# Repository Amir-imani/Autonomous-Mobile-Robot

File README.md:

# Autonomous Mobile Robot

Thesis project: **Design and Construction of a Mobile Robot with Intelligent Path Planning in Dynamic Environments**.

This repository contains the code, electronic design sources, and mechanical models for a differential-drive mobile robot. The software separates time-sensitive low-level control (RP2040), on-board ROS 2 integration (Raspberry Pi 5), and remote vision inference (external compute).

## Start here

- **[Software architecture and complete source guide](docs/SOFTWARE_GUIDE.md)** — subsystem flow, source-file descriptions, dependencies, how to navigate/run the code, and evidence limitations.
- **[Appendix A source index](docs/APPENDIX_CODE_INDEX.md)** — compact software source links for the thesis.
- **[Appendix B electrical design index](docs/APPENDIX_HARDWARE_INDEX.md)** — five circuit schematics, KiCad projects, PCB layouts and available fabrication outputs.
- **[Appendix C mechanical design index](docs/APPENDIX_MECHANICAL_INDEX.md)** — SolidWorks parts, drawings, manufacture quantities and materials.
- **[Code overview](code/README.md)** — package entry points.
- **[Experimental methodology](code/experiments/README.md)** — reproducible source checks, host emulations and hardware prerequisites.

## Repository layout

```text
code/
  firmware/pico/       RP2040 firmware, drivers, Neuro-PID training
  ros2/                Six ROS 2 packages: bridge, model, camera, GPU inference, messages, testbench
  experiments/         Source checks, host benchmarks, controlled emulation and analysis
hardware/              KiCad schematics, PCBs and manufacturing outputs
mechanical/            CAD and exported mechanical drawings
results/               Thesis results directory
docs/                  Appendix index and architecture guide
```

## Implementation scope and evidence

The repository contains closed-loop wheel-control firmware, sensor interfaces, a Pico ↔ Pi binary bridge, wheel odometry, LiDAR sample aggregation, robot description, compressed-image publication, a GPU-capable inference node, and experiment tooling. It does **not** bundle a complete evaluated Nav2/SLAM deployment, a trained ONNX model, or verified physical GPU performance results. Host emulations and software tests must be reported separately from physical measurements.

## Stable thesis citations

For final thesis citations, prefer a full commit-SHA URL (a fixed snapshot) instead of a moving `main` link. A release tag is optional and should only be cited after it actually exists. The repository is private; reviewers need authorized GitHub access.

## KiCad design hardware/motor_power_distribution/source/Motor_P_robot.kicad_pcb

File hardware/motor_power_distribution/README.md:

# Motor Power Distribution Board

This board distributes fused supply power to the robot's drive system and provides connections for an INA-series measurement module. It is a power-distribution board, not the BTS7960 motor driver or embedded motor-control firmware.

## Design files

- [KiCad schematic](source/Motor_P_robot.kicad_sch)
- [KiCad PCB](source/Motor_P_robot.kicad_pcb)
- [KiCad project](source/Motor_P_robot.kicad_pro)

## Manufacturing

Use the editable project as the source for ERC/DRC, pinout review, fabrication outputs and component verification. Check the current-monitor interface and power connector orientation against the as-built robot.

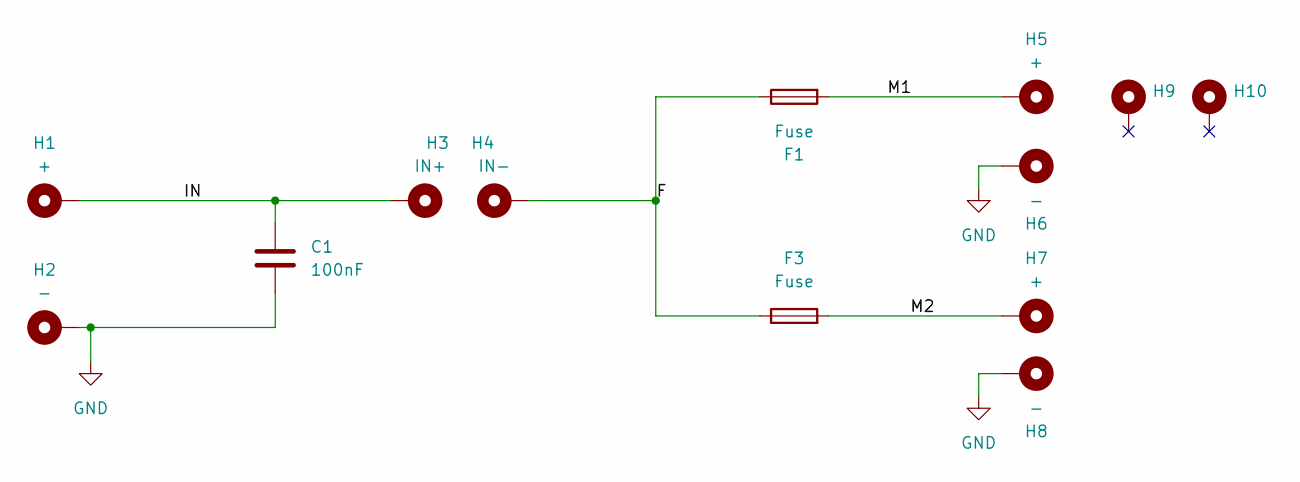
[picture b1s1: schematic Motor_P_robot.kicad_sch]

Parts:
C1: 100nF; C_1206_3216Metric_Pad1.33x1.80mm_HandSolder
F1, F3: Fuse; Fuse_Blade_ATO_directSolder
H1, H5, H7: +; MountingHole_2.2mm_M2_Pad_Via
H2, H6, H8: -; MountingHole_2.2mm_M2_Pad_Via
H3: IN+; MountingHole_2.2mm_M2_Pad_Via
H4: IN-; MountingHole_2.2mm_M2_Pad_Via
H9, H10: MountingHole_3.2mm_M3_Pad_Via

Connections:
/F: F1.1, F3.1, H4.1
/IN: C1.1, H1.1, H3.1
/M1: F1.2, H5.1
/M2: F3.2, H7.1
GND: C1.2, H2.1, H6.1, H8.1

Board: 2 copper layers, 13 parts (0 on the bottom side), 5 nets, no tracks yet.

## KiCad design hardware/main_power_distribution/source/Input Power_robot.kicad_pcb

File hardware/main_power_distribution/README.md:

# Main Power Distribution Board

The main power PCB provides input routing, fuse protection, transient suppression, filtering/bulk capacitors and connection points for an INA-series voltage/current monitoring module. Electrical values and pin assignments are defined in the editable schematic.

## Design files

- [KiCad schematic](source/Input%20Power_robot.kicad_sch)
- [KiCad PCB](source/Input%20Power_robot.kicad_pcb)
- [KiCad project](source/Input%20Power_robot.kicad_pro)

## Manufacturing

The editable KiCad source is the design reference. To manufacture a board, inspect footprints and connector assignments, run ERC/DRC, and generate Gerber/drill outputs from the approved board revision. The mounted INA-series measurement module should be identified from the physical assembly when compiling a final BOM.

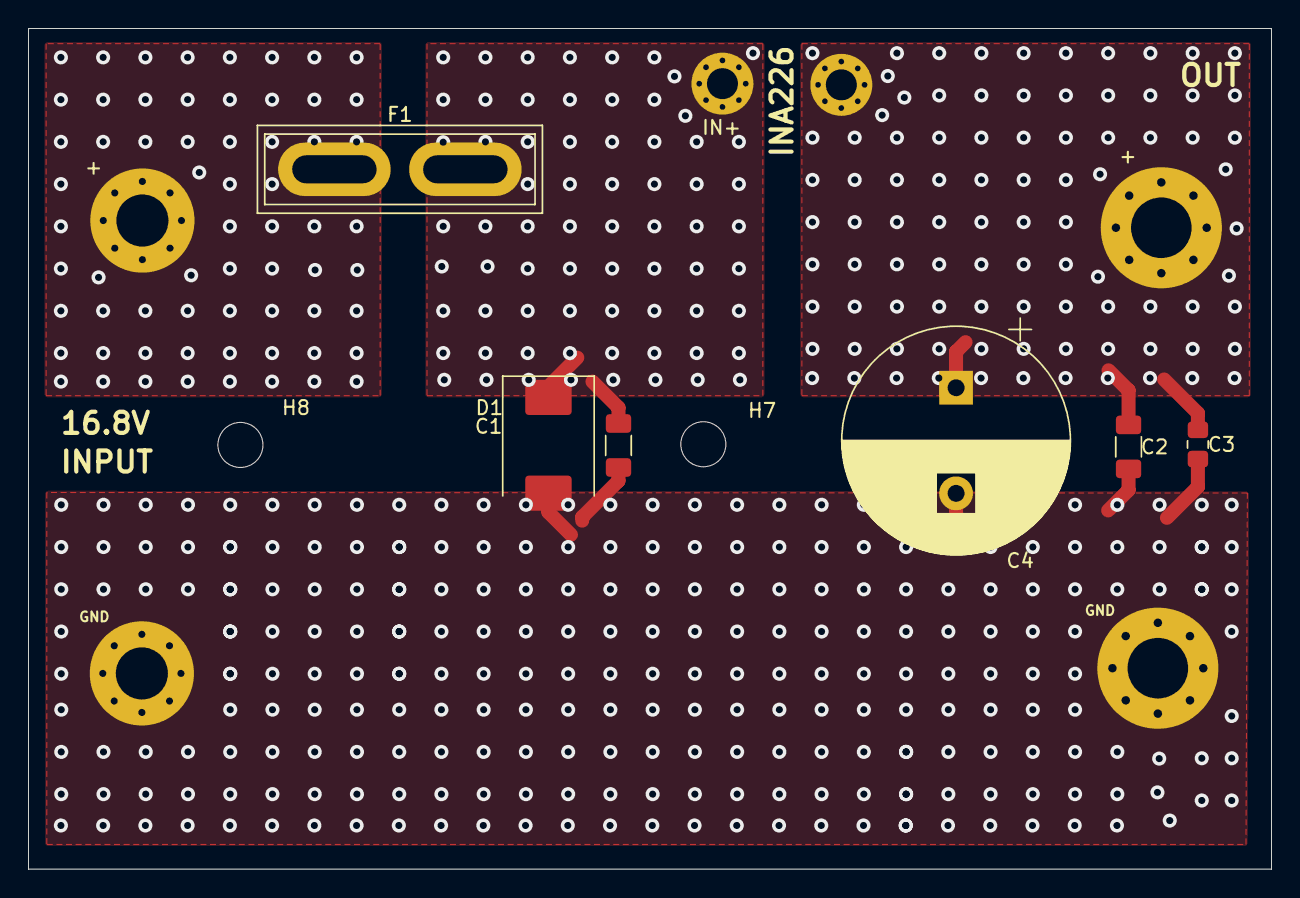
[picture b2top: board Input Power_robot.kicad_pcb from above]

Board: 2 copper layers, 88.3 x 59.7 mm, 14 parts (0 on the bottom side), 4 nets.

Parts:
+: IN; MountingHole_3.7mm_Pad_Via
+#2: OUT; MountingHole_4.3mm_M4_Pad_Via
C1, C2: 100nF; C_1206_3216Metric_Pad1.33x1.80mm_HandSolder
C3: 1uF; C_0805_2012Metric_Pad1.18x1.45mm_HandSolder
C4: 2200uF/35V; CP_Radial_D16.0mm_P7.50mm
D1: SMCJ18CA; D_SMC
F1: Fuse; Fuse_Blade_ATO_directSolder
GND: OUT; MountingHole_4.3mm_M4_Pad_Via
GND#2: IN; MountingHole_3.7mm_Pad_Via
H4: IN-; MountingHole_2.2mm_M2_Pad_Via
H7, H8: P; MountingHole_3.2mm_M3
IN+: IN+; MountingHole_2.2mm_M2_Pad_Via

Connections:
+16.8V: C1.1, D1.1 (A1), F1.2, IN+.1
+16.8V_R: +#2.1, C2.1, C3.1, C4.1, H4.1
+16.8V_U: +.1, F1.1
GND: C1.2, C2.2, C3.2, C4.2, D1.2 (A2), GND.1, GND#2.1

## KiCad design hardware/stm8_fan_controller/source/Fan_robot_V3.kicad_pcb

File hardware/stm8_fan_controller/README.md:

# STM8 Dual-Channel Temperature and Fan Controller

A custom thermal-management PCB for the autonomous mobile robot, based on the STM8S003F3P microcontroller.

## Hardware capabilities
- Two analog NTC thermistor inputs (ADC2 and ADC3).
- Two independently driven PWM fan channels (TIM2_CH1, TIM2_CH2), with TC4428A gate driver and Si9945BDY MOSFET switching stage.
- RGB status indicator driven through transistor stages (TIM1_CH1–CH3), supporting mixed colors.
- UART RX/TX connector for planned communication with the main Raspberry Pi Pico controller.
- SWIM/NRST programming connector.
- 5 V input and AMS1117-3.3 regulator for the logic rail.

## Thesis implementation status

**Hardware designed, fabricated, and mounted on the robot; not used as an active subsystem in the thesis experiments.** The schematics and PCB demonstrate the proposed thermal-management interface, but the board's actual temperature-feedback control, fan PWM response, UART exchange with the Pico, and RGB state logic must **not** be described as experimentally validated. The design repository documents the board at schematic and PCB level; active firmware-level operation is outside the reported experimental evaluation.

## Files

- `source/Fan_robot_V3.kicad_pro`: KiCad project settings.
- `source/Fan_robot_V3.kicad_sch`: Editable schematic.
- `source/Fan_robot_V3.kicad_pcb`: Editable PCB layout.
- `schematic/Fan_robot_V3.pdf`: One-page schematic for independent viewing.
- `images/pcb_3d_top.jpg`: 3D PCB render.

### PCB 3D render

### Schematic

[View schematic PDF](schematic/Fan_robot_V3.pdf)

## Fabrication and verification

Review footprints, connections, and thermal/power ratings using the schematic and PCB, and run ERC/DRC before fabrication. This documentation describes the circuit design and its installed role, not a measured closed-loop thermal-control performance.

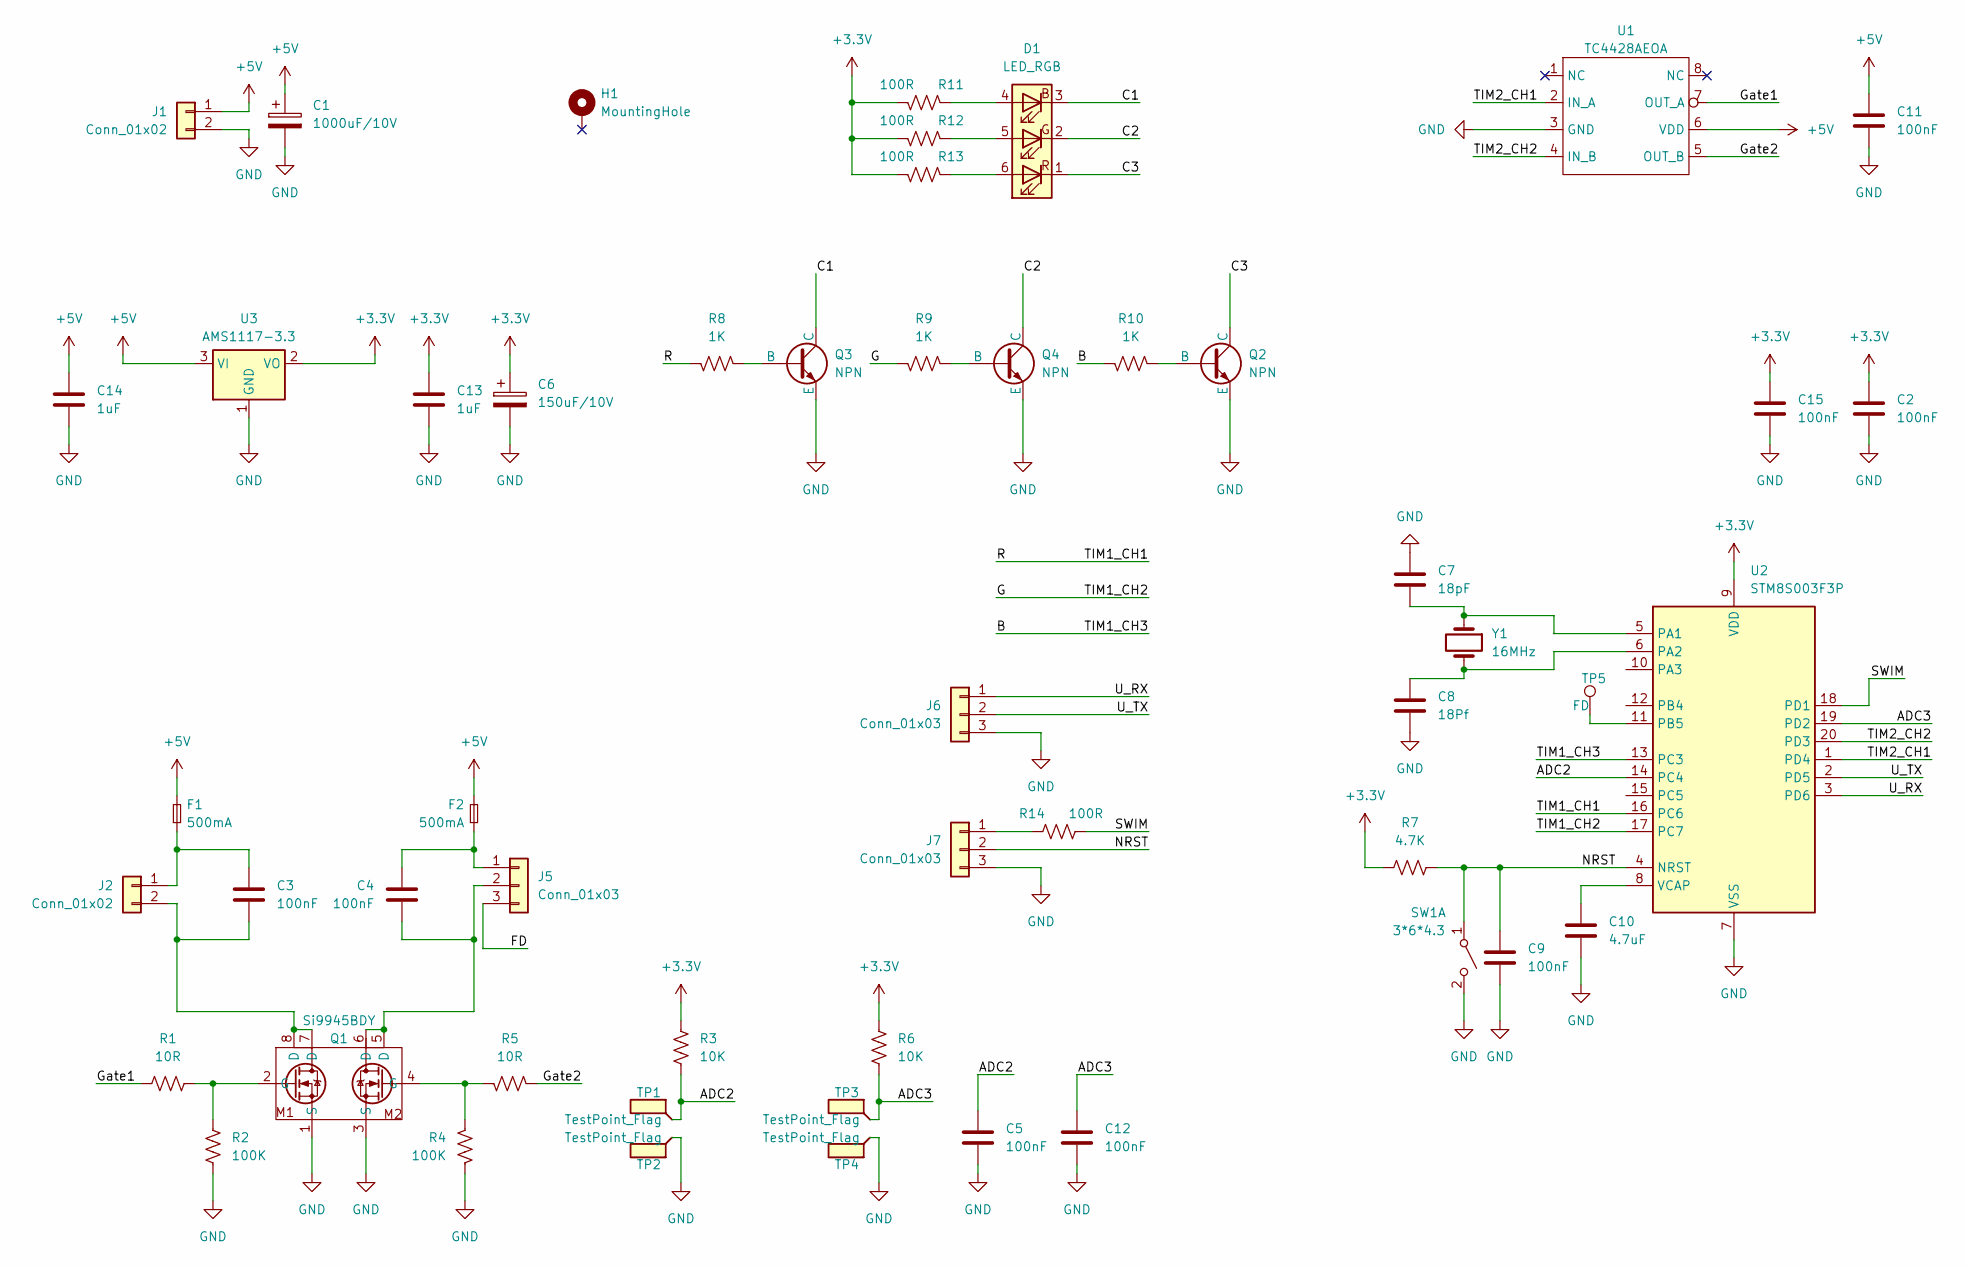
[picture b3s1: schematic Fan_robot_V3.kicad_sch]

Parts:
C1: 1000uF/10V; CP_Radial_D10.0mm_P5.00mm
C2, C3, C4, C5, C9, C11, C12, C15: 100nF; C_0805_2012Metric_Pad1.18x1.45mm_HandSolder
C6: 150uF/10V; CP_Elec_6.3x5.3
C7: 18pF; C_0805_2012Metric_Pad1.18x1.45mm_HandSolder
C8: 18Pf; C_0805_2012Metric_Pad1.18x1.45mm_HandSolder
C10: 4.7uF; C_0805_2012Metric_Pad1.18x1.45mm_HandSolder
C13, C14: 1uF; C_0805_2012Metric_Pad1.18x1.45mm_HandSolder
D1: LED_RGB; LED_RGB_5050-6
F1, F2: 500mA; Fuse_0805_2012Metric_Pad1.15x1.40mm_HandSolder
H1: MountingHole; MountingHole_3.2mm_M3_Pad_Via
J1: Conn_01x02; JST_XH_B2B-XH-A_1x02_P2.50mm_Vertical
J2: Conn_01x02; PinHeader_1x02_P2.54mm_Vertical
J5, J6, J7: Conn_01x03; PinHeader_1x03_P2.54mm_Vertical
Q1: Si9945BDY; PowerIntegrations_SO-8
Q2, Q3, Q4: NPN; SOT-23
R1, R5: 10R; R_0805_2012Metric_Pad1.20x1.40mm_HandSolder
R2, R4: 100K; R_0805_2012Metric_Pad1.20x1.40mm_HandSolder
R3, R6: 10K; R_0805_2012Metric_Pad1.20x1.40mm_HandSolder
R7: 4.7K; R_0805_2012Metric_Pad1.20x1.40mm_HandSolder
R8, R9, R10: 1K; R_0805_2012Metric_Pad1.20x1.40mm_HandSolder
R11, R12, R13, R14: 100R; R_0805_2012Metric_Pad1.20x1.40mm_HandSolder
SW1: 3*6*4.3; SW_Tactile_SPST_NO_Straight_CK_PTS636Sx25SMTRLFS
TP1, TP2, TP3, TP4: TestPoint_Flag; TestPoint_Pad_1.0x1.0mm
TP5: FD; TestPoint_Pad_D1.0mm
U1: TC4428AEOA; PowerIntegrations_SO-8
U2: STM8S003F3P; TSSOP-20_4.4x6.5mm_P0.65mm
U3: AMS1117-3.3; SOT-223-3_TabPin2
Y1: 16MHz; Crystal_SMD_HC49-SD

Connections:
+3.3V: C2.1, C6.1, C13.1, C15.1, R3.2, R6.2, R7.1, R11.2, R12.2, R13.2, U2.9 (VDD), U3.2 (VO)
+5V: C1.1, C11.1, C14.1, F1.2, F2.2, J1.1, U1.6 (VDD), U3.3 (VI)
/ADC2: C5.1, R3.1, TP1.1, U2.14 (PC4)
/ADC3: C12.1, R6.1, TP3.1, U2.19 (PD2)
/B: R10.2, U2.13 (PC3)
/C1: D1.3 (BK), Q3.3 (C)
/C2: D1.2 (GK), Q4.3 (C)
/C3: D1.1 (RK), Q2.3 (C)
/FD: J5.3
/G: R9.2, U2.17 (PC7)
/Gate1: R1.1, U1.7 (OUT_A)
/Gate2: R5.1, U1.5 (OUT_B)
/NRST: C9.1, J7.2, R7.2, SW1.1 (A), U2.4 (NRST)
/R: R8.2, U2.16 (PC6)
/SWIM: R14.2, U2.18 (PD1)
/TIM2_CH1: U1.2 (IN_A), U2.1 (PD4)
/TIM2_CH2: U1.4 (IN_B), U2.20 (PD3)
/U_RX: J6.1, U2.3 (PD6)
/U_TX: J6.2, U2.2 (PD5)
GND: C1.2, C2.2, C5.2, C6.2, C7.1, C8.2, C9.2, C10.2, C11.2, C12.2, C13.2, C14.2, C15.2, J1.2, J6.3, J7.3, Q1.1 (S), Q1.3 (S), Q2.2 (E), Q3.2 (E), Q4.2 (E), R2.1, R4.1, SW1.2 (B), TP2.1, TP4.1, U1.3 (GND), U2.7 (VSS), U3.1 (GND)
unnamed: D1.4 (BA), R11.1
unnamed: D1.5 (GA), R12.1
unnamed: D1.6 (RA), R13.1
unnamed: C3.1, F1.1, J2.1
unnamed: C3.2, J2.2, Q1.7 (D), Q1.8 (D)
unnamed: C4.1, F2.1, J5.1
unnamed: C4.2, J5.2, Q1.5 (D), Q1.6 (D)
unnamed: J7.1, R14.1
unnamed: Q1.2 (G), R1.2, R2.2
unnamed: Q1.4 (G), R4.2, R5.2
unnamed: Q2.1 (B), R10.1
unnamed: Q3.1 (B), R8.1
unnamed: Q4.1 (B), R9.1
unnamed: C7.2, U2.5 (PA1), Y1.1
unnamed: C8.1, U2.6 (PA2), Y1.2
unnamed: TP5.1, U2.11 (PB5)
unnamed: C10.1, U2.8 (VCAP)

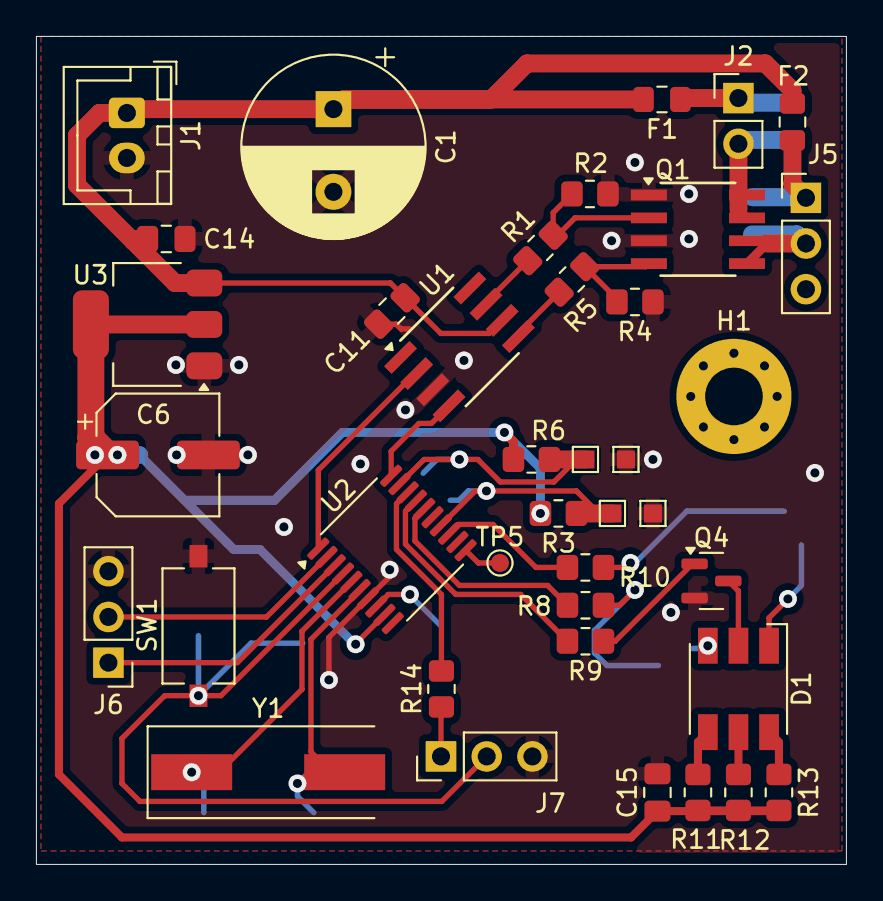
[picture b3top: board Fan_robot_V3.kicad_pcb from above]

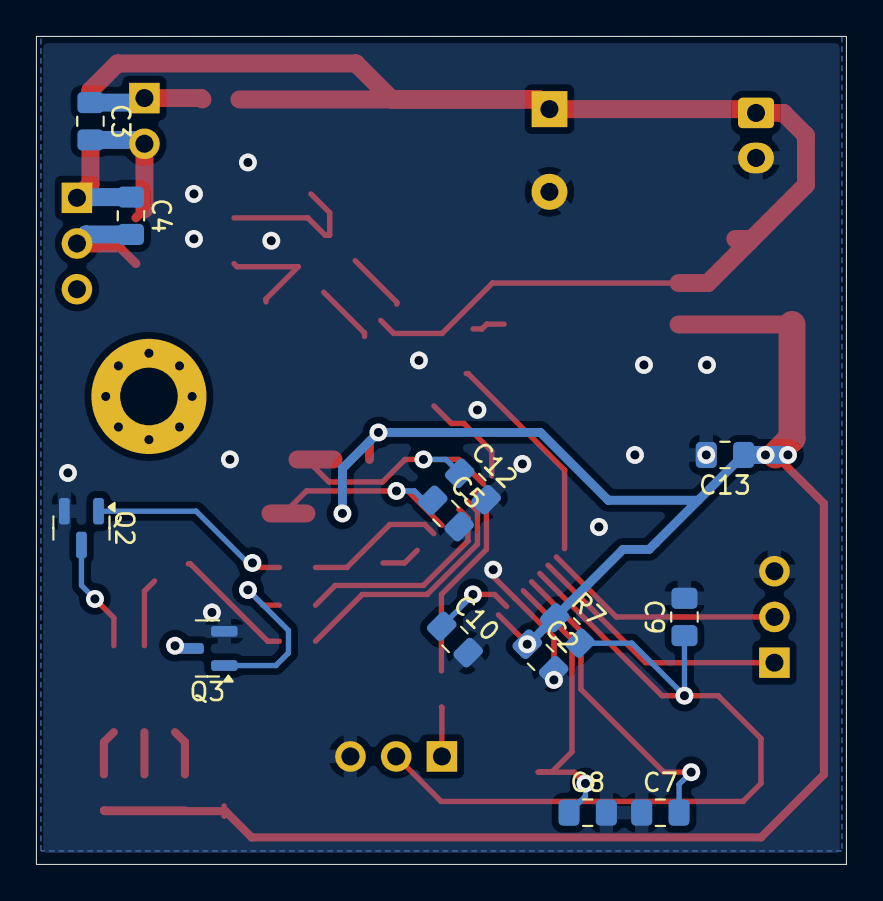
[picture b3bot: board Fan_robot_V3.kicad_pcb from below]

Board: 2 copper layers, 45.0 x 46.0 mm, 52 parts (13 on the bottom side), 36 nets.

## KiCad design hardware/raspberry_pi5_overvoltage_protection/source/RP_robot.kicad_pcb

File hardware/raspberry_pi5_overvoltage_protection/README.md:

# Raspberry Pi 5 Overvoltage Protection Board

This directory contains the KiCad design sources, manufacturing outputs, and design views for the custom Raspberry Pi 5 power-protection board used in the mobile robot.

## Purpose

The board is intended to protect the Raspberry Pi 5 supply rail against an overvoltage event around the 5.1 V threshold. The submitted schematic uses a 5.1 V Zener-triggered crowbar-style protection stage together with a 5 A input fuse and transient suppression.

The editable KiCad source is the authoritative design record. The Gerber and drill files are a fabrication snapshot generated from that design.

## Repository contents

```text
raspberry_pi5_overvoltage_protection/
├── source/
│   ├── RP_robot.kicad_pro
│   ├── RP_robot.kicad_sch
│   └── RP_robot.kicad_pcb
├── fabrication/
│   ├── gerber/
│   │   ├── F_Cu / B_Cu
│   │   ├── F_Mask / B_Mask
│   │   ├── F_Paste / B_Paste
│   │   ├── F_Silkscreen / B_Silkscreen
│   │   ├── Edge_Cuts
│   │   └── Gerber job file
│   └── drill/
│       ├── PTH
│       └── NPTH
└── images/
    ├── pcb_3d_top.png
    └── schematic_view.png
```

## Design views

### 3D PCB render

### Schematic view

## Notes

The schematic snapshot includes the 5.1 V Zener threshold element, a 5 A fuse, an SMBJ5.0A TVS device, and thyristor-based protection devices. Actual trip voltage and fault-clearing behavior depend on component tolerances, fuse characteristics, wiring resistance, and the upstream power source; these should be verified on the physical board before relying on the circuit as the sole protection mechanism.

## Thesis appendix

For the thesis appendix, the schematic view and 3D PCB render are the most useful visual artifacts. The complete KiCad and manufacturing files are preserved here for reproducibility.

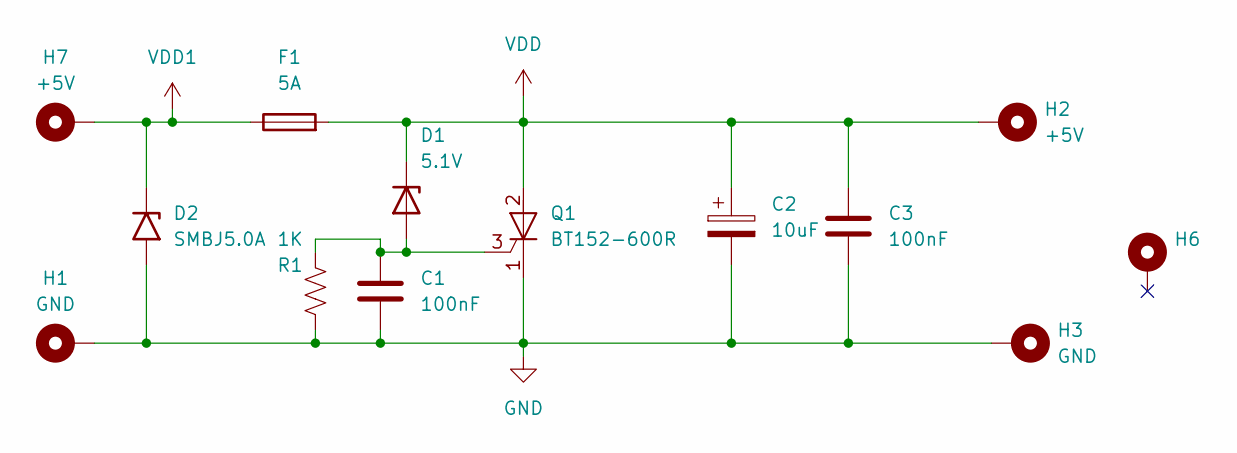
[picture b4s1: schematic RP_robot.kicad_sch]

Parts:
C1, C3: 100nF; C_0805_2012Metric_Pad1.18x1.45mm_HandSolder
C2: 10uF; CP_Elec_6.3x5.3
D1: 5.1V; D_MELF
D2: SMBJ5.0A; D_SMB
F1: 5A; Fuse_1206_3216Metric_Pad1.42x1.75mm_HandSolder
H1, H3: GND; MountingHole_2.2mm_M2_Pad_Via
H2, H7: +5V; MountingHole_2.2mm_M2_Pad_Via
H6: +5V; MountingHole_3.2mm_M3
Q1: BT152-600R; TO-218-3_Horizontal_TabDown
R1: 1K; R_0805_2012Metric_Pad1.20x1.40mm_HandSolder

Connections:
GND: C1.2, C2.2, C3.2, D2.2 (A2), H1.1, H3.1, Q1.1 (K), R1.2
unnamed: C1.1, D1.2 (A), Q1.3 (G), R1.1
VDD: C2.1, C3.1, D1.1 (K), F1.2, H2.1, Q1.2 (A)
VDD1: D2.1 (A1), F1.1, H7.1

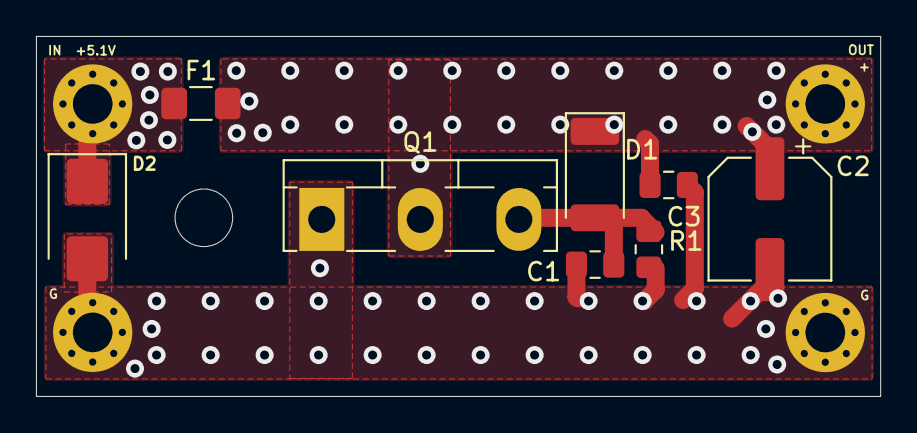
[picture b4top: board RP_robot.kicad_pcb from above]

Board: 2 copper layers, 46.9 x 20.0 mm, 13 parts (0 on the bottom side), 4 nets.

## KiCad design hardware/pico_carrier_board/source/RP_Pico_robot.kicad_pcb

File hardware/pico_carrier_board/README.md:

# Raspberry Pi Pico Carrier / Header Board

This directory contains the hardware design files for the custom Raspberry Pi Pico carrier/header board used in the mobile robot.

## Repository contents

```text
pico_carrier_board/
├── source/
│   ├── RP_Pico_robot.kicad_pro
│   ├── RP_Pico_robot.kicad_sch
│   └── RP_Pico_robot.kicad_pcb
├── fabrication/
│   ├── gerber/
│   │   ├── F_Cu / B_Cu
│   │   ├── F_Mask / B_Mask
│   │   ├── F_Paste / B_Paste
│   │   ├── F_Silkscreen / B_Silkscreen
│   │   ├── Edge_Cuts
│   │   └── Gerber job file
│   └── drill/
│       ├── PTH
│       └── NPTH
└── images/
    ├── pcb_3d_top.jpg
    ├── pcb_3d_bottom.jpg
    └── pcb_layout_editor.jpg
```

## Design role

The board serves as the Raspberry Pi Pico interface/carrier for the robot electronics. It breaks out Pico I/O and power rails through labeled connectors for the robot subsystems and provides the physical integration point between the RP2040 controller and the low-level electronics.

The editable KiCad project under `source/` is the authoritative design source. The Gerber and drill files are manufacturing outputs generated from this design snapshot.

## Design views

### Top-side 3D render

### Bottom-side 3D render

### PCB Editor layout

## Fabrication snapshot

The supplied Gerber and drill outputs were generated by **KiCad/Pcbnew 10.0.3** on **2026-09-11**.

Before ordering a new production batch:

1. Open the editable KiCad project.
2. Run ERC/DRC.
3. Verify footprints and connector orientation against the assembled hardware.
4. Regenerate Gerber and drill files if the source design has changed.

## Thesis appendix

For the thesis appendix, the most useful figures are the PCB Editor layout plus the top and bottom 3D renders. The complete KiCad source and manufacturing outputs remain in the repository so the board can be inspected independently of the thesis document.

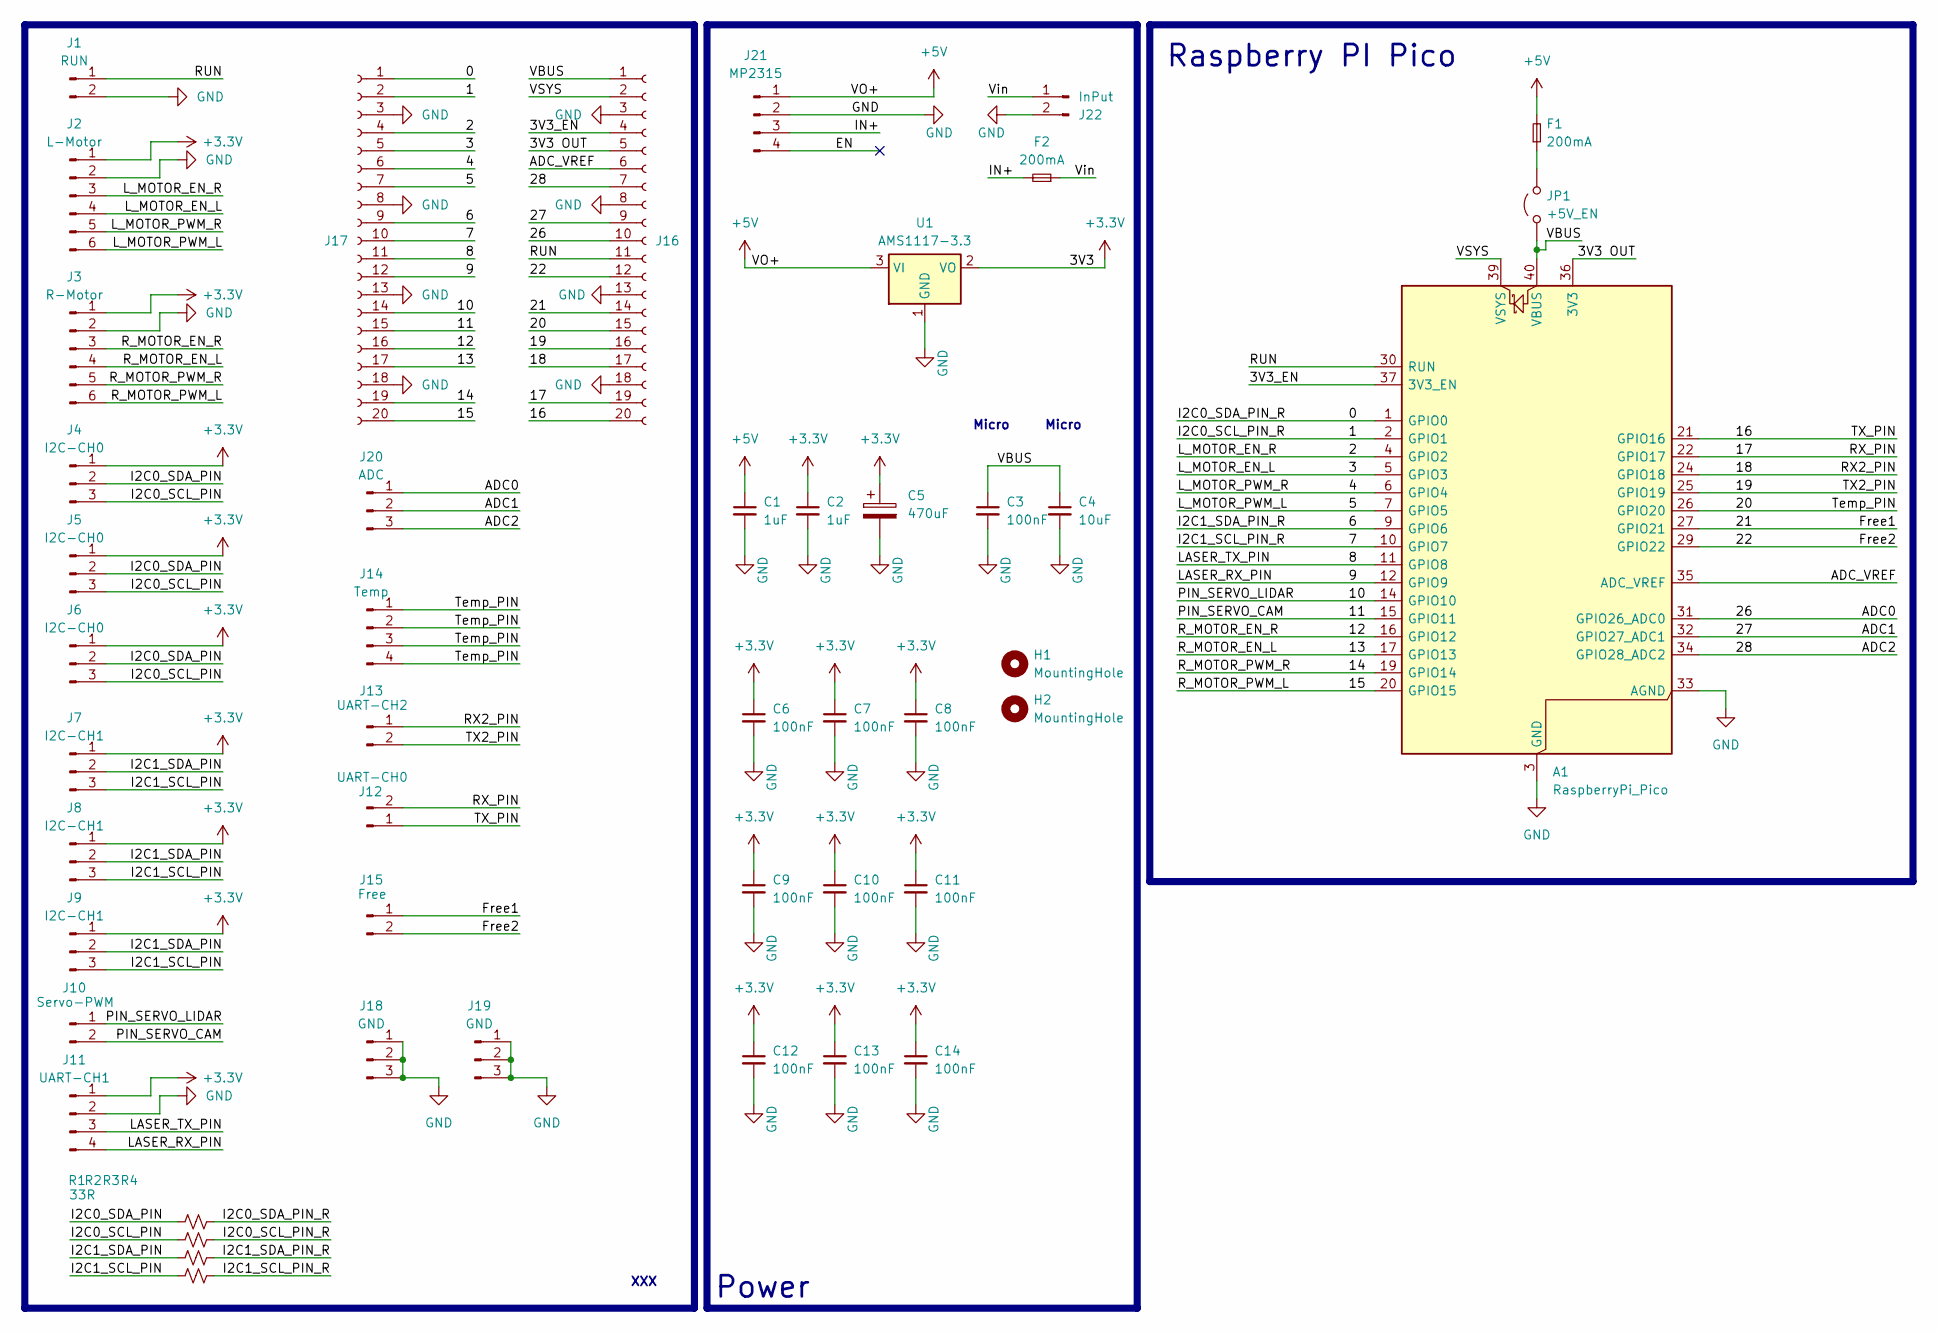
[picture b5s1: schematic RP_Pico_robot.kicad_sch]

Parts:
A1: RaspberryPi_Pico; RaspberryPi_Pico_Common_Unspecified
C1, C2: 1uF; C_0805_2012Metric_Pad1.18x1.45mm_HandSolder
C3, C6, C7, C8, C9, C10, C11, C12, C13, C14: 100nF; C_0805_2012Metric_Pad1.18x1.45mm_HandSolder
C4: 10uF; C_0805_2012Metric_Pad1.18x1.45mm_HandSolder
C5: 470uF; CP_Radial_D8.0mm_P3.80mm
F1, F2: 200mA; Fuse_0805_2012Metric_Pad1.15x1.40mm_HandSolder
H1, H2: MountingHole; MountingHole_3mm_Pad_Via
J1: RUN; JST_XH_B2B-XH-A_1x02_P2.50mm_Vertical
J2: L-Motor; JST_XH_B6B-XH-A_1x06_P2.50mm_Vertical
J3: R-Motor; JST_XH_B6B-XH-A_1x06_P2.50mm_Vertical
J4, J5, J6: I2C-CH0; JST_XH_B3B-XH-A_1x03_P2.50mm_Vertical
J7, J8, J9: I2C-CH1; JST_XH_B3B-XH-A_1x03_P2.50mm_Vertical
J10: Servo-PWM; JST_XH_B2B-XH-A_1x02_P2.50mm_Vertical
J11: UART-CH1; JST_XH_B4B-XH-A_1x04_P2.50mm_Vertical
J12: UART-CH0; JST_XH_B2B-XH-A_1x02_P2.50mm_Vertical
J13: UART-CH2; JST_XH_B2B-XH-A_1x02_P2.50mm_Vertical
J14: Temp; JST_XH_B4B-XH-A_1x04_P2.50mm_Vertical
J15: Free; JST_XH_B2B-XH-A_1x02_P2.50mm_Vertical
J16, J17: Conn_01x20_Socket; PinHeader_1x20_P2.54mm_Vertical
J18, J19: GND; JST_XH_B3B-XH-A_1x03_P2.50mm_Vertical
J20: ADC; JST_XH_B3B-XH-A_1x03_P2.50mm_Vertical
J21: MP2315; PinHeader_1x04_P2.54mm_Vertical
J22: InPut; JST_XH_B2B-XH-A_1x02_P2.50mm_Vertical
JP1: +5V_EN; TestPoint_2Pads_Pitch2.54mm_Drill0.8mm
R1, R2, R3, R4: 33R; R_0805_2012Metric_Pad1.20x1.40mm_HandSolder
U1: AMS1117-3.3; SOT-223-3_TabPin2

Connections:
+3.3V: C2.1, C5.1, C6.1, C7.1, C8.1, C9.1, C10.1, C11.1, C12.1, C13.1, C14.1, J2.1, J3.1, J4.1, J5.1, J6.1, J7.1, J8.1, J9.1, J11.1, U1.2 (VO)
+5V: C1.1, F1.2, J21.1, U1.3 (VI)
/0: A1.1 (GPIO0), J17.1, R1.2
/1: A1.2 (GPIO1), J17.2, R2.2
/2: A1.4 (GPIO2), J2.3, J17.4
/3: A1.5 (GPIO3), J2.4, J17.5
/3V3 OUT: A1.36 (3V3), J16.5
/3V3_EN: A1.37 (3V3_EN), J16.4
/4: A1.6 (GPIO4), J2.5, J17.6
/5: A1.7 (GPIO5), J2.6, J17.7
/6: A1.9 (GPIO6), J17.9, R3.2
/7: A1.10 (GPIO7), J17.10, R4.2
/8: A1.11 (GPIO8), J11.3, J17.11
/9: A1.12 (GPIO9), J11.4, J17.12
/10: A1.14 (GPIO10), J10.1, J17.14
/11: A1.15 (GPIO11), J10.2, J17.15
/12: A1.16 (GPIO12), J3.3, J17.16
/13: A1.17 (GPIO13), J3.4, J17.17
/14: A1.19 (GPIO14), J3.5, J17.19
/15: A1.20 (GPIO15), J3.6, J17.20
/16: A1.21 (GPIO16), J12.1, J16.20
/17: A1.22 (GPIO17), J12.2, J16.19
/18: A1.24 (GPIO18), J13.1, J16.17
/19: A1.25 (GPIO19), J13.2, J16.16
/20: A1.26 (GPIO20), J14.1, J14.2, J14.3, J14.4, J16.15
/21: A1.27 (GPIO21), J15.1, J16.14
/22: A1.29 (GPIO22), J15.2, J16.12
/26: A1.31 (GPIO26_ADC0), J16.10, J20.1
/27: A1.32 (GPIO27_ADC1), J16.9, J20.2
/28: A1.34 (GPIO28_ADC2), J16.7, J20.3
/ADC_VREF: A1.35 (ADC_VREF), J16.6
/EN: J21.4
/I2C0_SCL_PIN: J4.3, J5.3, J6.3, R2.1
/I2C0_SDA_PIN: J4.2, J5.2, J6.2, R1.1
/I2C1_SCL_PIN: J7.3, J8.3, J9.3, R4.1
/I2C1_SDA_PIN: J7.2, J8.2, J9.2, R3.1
/IN+: F2.2, J21.3
/RUN: A1.30 (RUN), J1.1, J16.11
/VBUS: A1.40 (VBUS), C3.1, C4.1, J16.1, JP1.1 (A)
/VSYS: A1.39 (VSYS), J16.2
/Vin: F2.1, J22.1
GND: A1.3 (GND), A1.8 (GND), A1.13 (GND), A1.18 (GND), A1.23 (GND), A1.28 (GND), A1.33 (AGND), A1.38 (GND), C1.2, C2.2, C3.2, C4.2, C5.2, C6.2, C7.2, C8.2, C9.2, C10.2, C11.2, C12.2, C13.2, C14.2, J1.2, J2.2, J3.2, J11.2, J16.3, J16.8, J16.13, J16.18, J17.3, J17.8, J17.13, J17.18, J18.1, J18.2, J18.3, J19.1, J19.2, J19.3, J21.2, J22.2, U1.1 (GND)
unnamed: F1.1, JP1.2 (B)

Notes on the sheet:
XXX
Raspberry PI Pico
Micro
Power

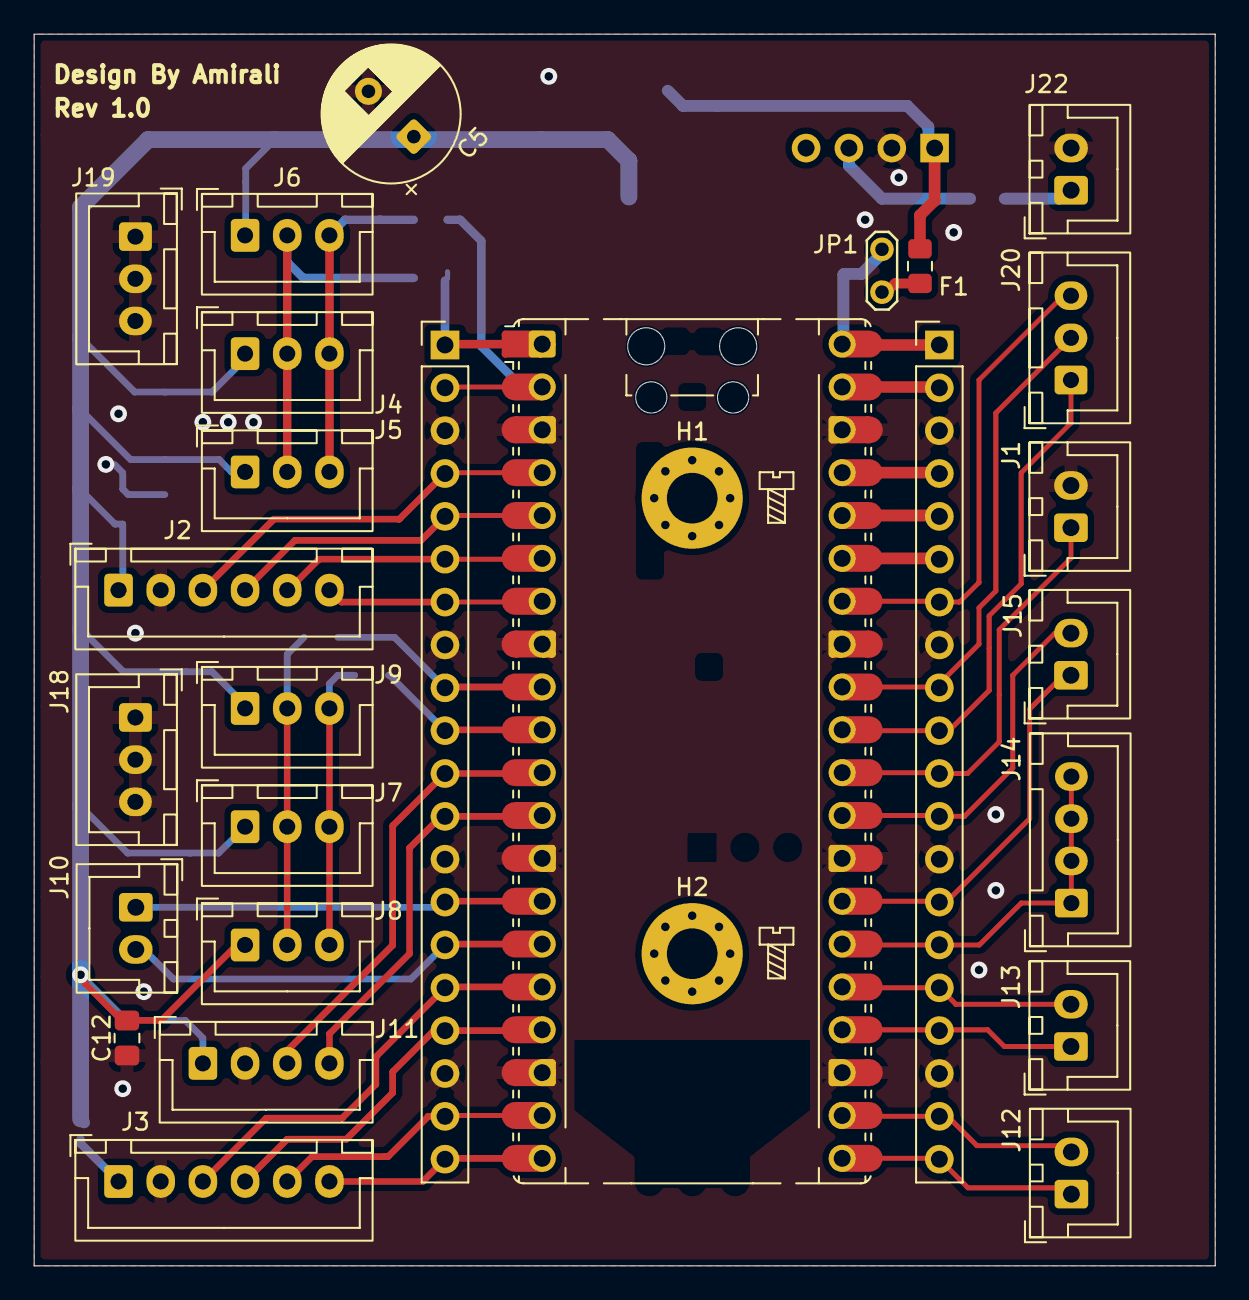
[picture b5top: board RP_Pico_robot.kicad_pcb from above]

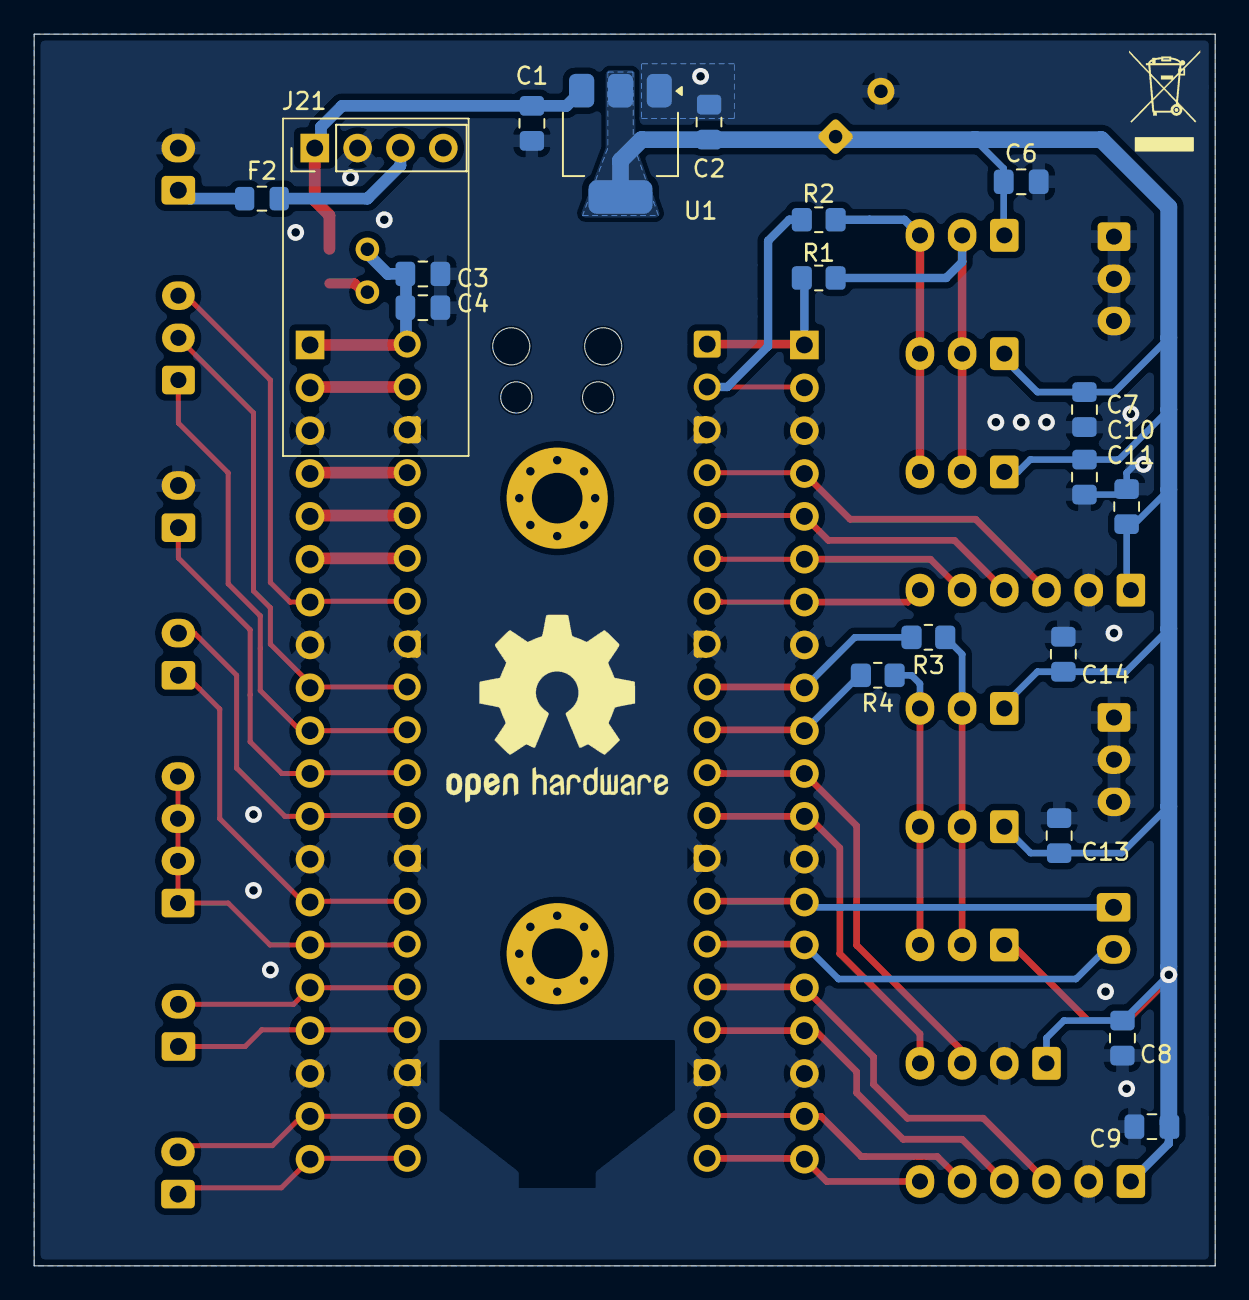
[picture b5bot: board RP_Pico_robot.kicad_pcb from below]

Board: 2 copper layers, 70.0 x 73.0 mm, 47 parts (19 on the bottom side), 42 nets.

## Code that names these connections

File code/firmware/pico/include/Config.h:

#ifndef CONFIG_H
#define CONFIG_H

// ==========================================
// Motor Driver BTS7960
// ==========================================
// Left
#define L_MOTOR_EN_R  2
#define L_MOTOR_EN_L  3
#define L_MOTOR_PWM_R 4
#define L_MOTOR_PWM_L 5
#define L_MOTOR_INVERT true

// Right
#define R_MOTOR_EN_R  12
#define R_MOTOR_EN_L  13
#define R_MOTOR_PWM_R 14
#define R_MOTOR_PWM_L 15
#define R_MOTOR_INVERT false


#define GEAR_RATIO 110.0

// ==========================================
// 2. Servo
// ==========================================

#define PIN_SERVO_LIDAR 10
#define PIN_SERVO_CAM   11
#define SERVO_MIN_PULSE 544
#define SERVO_MAX_PULSE 2400
#define LIDAR_SERVO_SPEED_DEG_PER_SEC 85.0f
#define SERVO_CONTROL_INTERVAL_MS    20U

// ==========================================
// 3. I2C & UART
// ==========================================
// I2C0 :
#define I2C0_SDA_PIN 0
#define I2C0_SCL_PIN 1

// I2C1 :
#define I2C1_SDA_PIN 26
#define I2C1_SCL_PIN 27

// UART : 
#define LASER_TX_PIN 8
#define LASER_RX_PIN 9
#define LASER_BAUDRATE 9600

// ==========================================
// RTOS Scheduler
// ==========================================

#define TASK_IMU_INTERVAL_MS    10  // 100 Hz
#define TASK_MOTOR_INTERVAL_MS  20  // 50 Hz
#define TASK_LIDAR_INTERVAL_MS  20  // 50 Hz servo command update
#define TASK_TELEMETRY_INTERVAL_MS 20  // 50 Hz binary telemetry
#define TASK_DIAGNOSTIC_INTERVAL_MS 100 // 10 Hz USB diagnostics

// ==========================================
// Bench safety profile
// ==========================================
// Set this to 0 before operating the robot with drive wheels on the ground.
// Bench mode preserves the hardware watchdog and command stop behavior, but
// prevents encoder or power-monitor I2C faults from disabling suspended wheels.
#define BENCH_TEST_MODE 1

#if BENCH_TEST_MODE
#define COMMAND_STALE_TIMEOUT_MS 500U
#define SENSOR_STALE_TIMEOUT_MS  150U
#else
#define COMMAND_STALE_TIMEOUT_MS 100U
#define SENSOR_STALE_TIMEOUT_MS  100U
#endif

#endif
